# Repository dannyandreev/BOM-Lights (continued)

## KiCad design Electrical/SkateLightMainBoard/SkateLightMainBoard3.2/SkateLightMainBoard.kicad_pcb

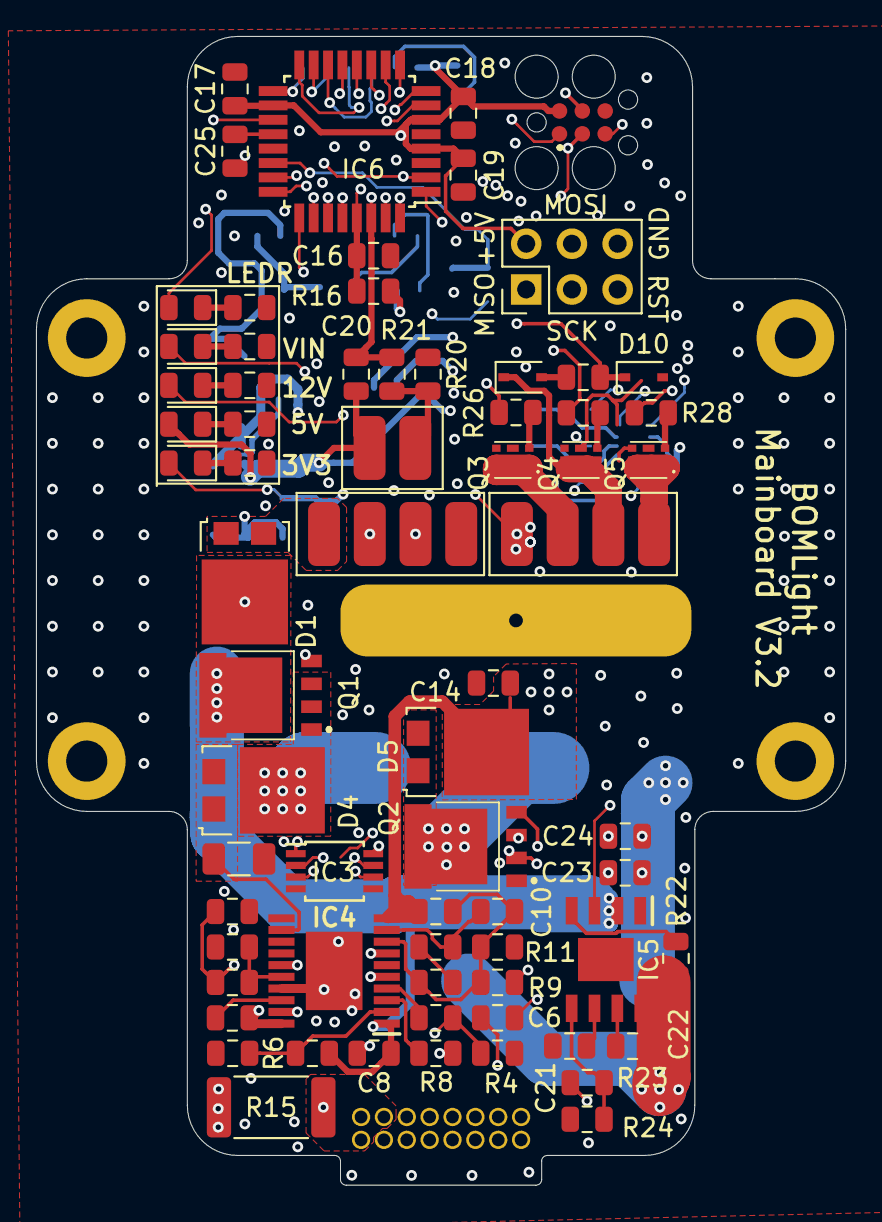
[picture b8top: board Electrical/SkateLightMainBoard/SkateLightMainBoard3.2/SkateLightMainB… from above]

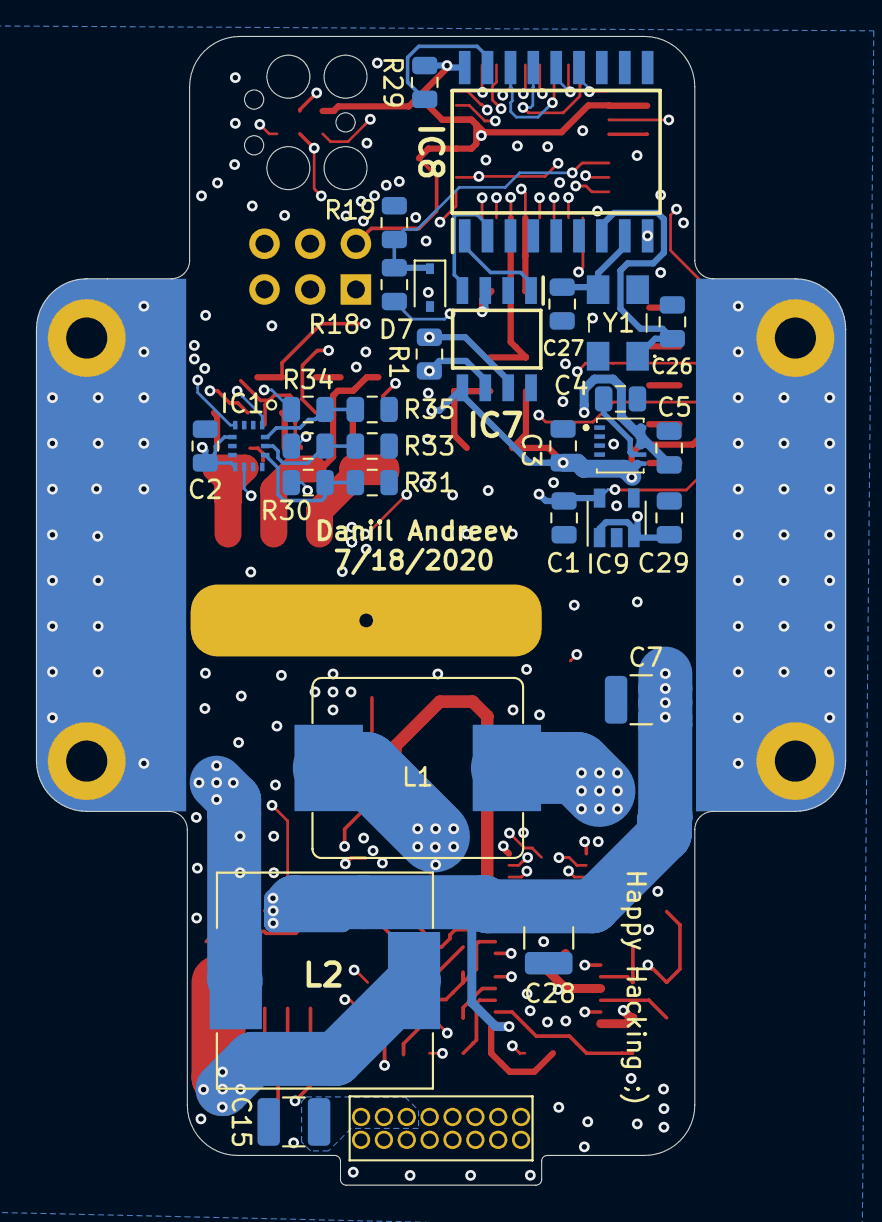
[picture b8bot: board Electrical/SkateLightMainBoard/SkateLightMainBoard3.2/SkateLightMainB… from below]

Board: 4 copper layers, 45.0 x 63.8 mm, 103 parts (31 on the bottom side), 78 nets.

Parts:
C1, C3, C23, C24: 10uF 16V; C_0805_2012Metric
C2, C16, C17, C18, C19, C20, C25: 0.1uF 25V; C_0805_2012Metric
C4, C13, C21, C29: 1uF 25V; C_0805_2012Metric
C5: 1uF 100V; C_0805_2012Metric
C6: 22nF 100V; C_0805_2012Metric
C7, C15, C28: 10uF 100V; C_1210_3225Metric
C8, C9, C11, C14, C22: 0.1uF 100V; C_0805_2012Metric
C10, C12: 2.2nF 100V; C_0805_2012Metric
C26, C27: 27pF 25V; C_0805_2012Metric
D1, D4, D5: D_Schottky_AAK; TO-277A
D2, D3, D8, D9: LEDO; LED_0805_2012Metric
D6: LEDR; LED_0805_2012Metric
D7, D10: 3V6 5%; D_SOD-323
D11: D; D_SOD-323
H1: MountingHole_Pad; ThermalPadV2_SkateLight_L
H2: MountingHole_Pad; ThermalPadV2_SkateLight_R
H3: MountingHole; Wire Slot 1
IC1: LSM6DS3USTR; LGA-14(2.5X3X0.86)
IC2: MAXM15062AMB+; MAXM15462AMB
IC3: MCP4132-502E_SN; TSSOP-8_3x3mm_P0.65mm
IC4: LM5118MH_NOPB; SOP65P640X110-21N
IC5: LMR36520FADDAR; SOIC127P600X170-9N
IC6: ATMEGA328P-AUR; TQFP-32_7x7mm_P0.8mm
IC7: MCP2562-E_SN; SOIC127P600X175-8N
IC8: MCP2515T-I_SO; SOIC127P1030X265-18N
IC9: AP2139AK-3.3TRG1; SOT-23-5
J1, J7: Conn_01x04_Male; 4 Wire Pad
J2: Conn_02x03_Odd_Even; PinHeader_2x03_P2.54mm_Vertical
J3: Conn_02x08_Odd_Even; Conn_2x8_0.05in
J4: TC2030-MCP; TC2030MCP
J6: Conn_01x02_Male; 2WirePad
L1: 97uH 2.7A; ‎ETQ-P5M101YGC‎ Inductor
L2: 7447709330‎ 33uH 4.2A 45MOHM; WE-PD_1260%2f1245%2f1280%2f121054
Q1, Q2: PSMN039-100YS,115; PSMN5R660YLX
Q3, Q4, Q5: FDMA410NZ
R1: 120 5%; R_0805_2012Metric
R2: 33k 5%; R_0805_2012Metric
R3, R31, R33, R35: 3k3 5%; R_0805_2012Metric
R4: 47k 5%; R_0805_2012Metric
R5: 1k 5%; R_0805_2012Metric
R6: 68k 5%; R_0805_2012Metric
R7, R12, R16, R21, R25, R29: 10k 5%; R_0805_2012Metric
R8: 20k5 1%; R_0805_2012Metric
R9: 330 1%; R_0805_2012Metric
R10: 47k 1%; R_0805_2012Metric
R11: 22k 1%; R_0805_2012Metric
R13: 36k5 1%; R_0805_2012Metric
R14: 0.03 1% 0.5W; R_1206_3216Metric
R15: 0.3 1% 1W; R_2512_6332Metric
R17: 1k5 5%; R_0805_2012Metric
R18, R20: 100k 5%; R_0805_2012Metric
R19: 4k7 5%; R_0805_2012Metric
R22: 100k %5; R_0805_2012Metric
R23: 100k 1%; R_0805_2012Metric
R24: 9.09 1%; R_0805_2012Metric
R26, R27, R28, R37: 330 5%; R_0805_2012Metric
R30, R32, R34: 2k2 5%; R_0805_2012Metric
R36: 1k2 5%; R_0805_2012Metric
Y1: ECS-80-18-30B-AGN-TR; ECS801830BAGNTR

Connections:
12V_CTRL: IC5.3, IC6.8
+3V3: C1.1, C2.1, D9.2, IC1.5, IC1.8, IC9.5
+5V: C3.1, C17.1, C18.1, C19.1, C20.1, C29.1, D3.2, IC2.5, IC2.6, IC3.8, IC6.4, IC6.6, IC6.18, IC7.3, IC7.5, IC8.18, IC9.1, IC9.3, J2.2, J3.13, J4.2, J6.2, R16.1, R29.1
+12V: C23.1, C24.1, D8.2, J7.4, L2.2, R23.2
/CAN Controller/CANH: IC7.7, J1.3, R1.2
/CAN Controller/CANL: IC7.6, J1.2, R1.1
Button: C20.2, IC6.30, R21.1
CTRLLEDB: IC6.13, R28.1
CTRLLEDG: IC6.10, R27.1
CTRLLEDR: IC6.9, R26.1
GND: C1.2, C2.2, C3.2, C4.2, C5.2, C6.2, C7.2, C8.2, C12.2, C13.2, C14.2, C15.2, C16.2, C17.2, C18.2, C19.2, C21.2, C23.2, C24.2, C25.2, C26.2, C27.2, C28.2, C29.2, D7.2, D10.2, H1.1, H2.1, IC1.2, IC1.3, IC1.6, IC1.7, IC2.2, IC3.4, IC3.5, IC4.6, IC4.13, IC4.14, IC4.17, IC4.21, IC5.1, IC5.9, IC6.3, IC6.5, IC6.21, IC7.2, IC7.8, IC8.9, IC9.2, J1.1, J2.6, J3.7, J4.6, Q2.1, Q2.2, Q2.3, Q3.4, Q3.8, Q4.4, Q4.8, Q5.4, Q5.8, R2.2, R3.2, R4.2, R7.2, R8.2, R11.2, R14.2, R15.2, R17.2, R19.2, R20.1, R24.1, R25.2, R31.2, R33.2, R35.2, R36.2, Y1.2, Y1.4
IMU_INT1: IC1.4, IC6.31
IMU_INT2: IC1.9, IC6.32
LED+: C14.1, C15.1, D5.3, IC4.10, J3.2, J3.4, J3.6, R10.1
LED-: IC6.19, J3.14, J3.15, J3.16, R15.1
LEDCTRL: IC6.1, R4.1, R5.2
LEDR: D6.2, IC6.2
LEDSign1: IC6.27, J3.11
LEDSign2: IC6.28, J3.12
LightSense1: IC6.25, J3.8
LightSense2: IC6.26, J3.9
NRST: C16.1, IC6.29, J2.5, J4.5, R16.2
unnamed: C4.1, IC2.7
unnamed: C6.1, IC4.7
unnamed: C9.1, R12.2
unnamed: C10.1, IC4.9, R12.1
unnamed: C9.2, C10.2, IC4.8, R9.1, R10.2, R11.1
unnamed: C11.1, D4.3, IC4.20, L1.1, Q1.1, Q1.2, Q1.3
unnamed: C11.2, IC4.18
unnamed: C12.1, IC4.5, R13.2
unnamed: C13.1, IC4.16, R13.1
unnamed: C21.1, IC5.6
unnamed: C22.1, IC5.8, L2.1, R22.2
unnamed: C22.2, IC5.7
unnamed: C25.1, IC6.20
unnamed: D1.1, D1.2, J1.4
unnamed: D2.1, R2.1
unnamed: D3.1, R3.1
unnamed: D4.1, D4.2, IC4.12, R14.1
unnamed: D5.1, D5.2, L1.2, Q2.5
unnamed: D6.1, R17.1
unnamed: D8.1, R25.1
unnamed: D9.1, R36.1
unnamed: D11.1, J7.2, Q4.1, Q4.2, Q4.5, Q4.6, Q4.7
unnamed: D11.2, R37.1
unnamed: IC1.12, R30.2, R31.1
unnamed: IC1.13, R32.2, R33.1
unnamed: IC1.14, R34.2, R35.1
unnamed: IC3.6, R9.2
unnamed: IC4.2, R6.2, R7.1
unnamed: IC4.3, R8.1
unnamed: IC4.4, R5.1
unnamed: IC4.15, Q2.4
unnamed: IC4.19, Q1.4
unnamed: IC5.4, R22.1
unnamed: IC5.5, R23.1, R24.2
unnamed: IC7.1, IC8.1
unnamed: IC7.4, IC8.2
unnamed: IC8.17, R29.2
unnamed: J6.1, R20.2, R21.2
unnamed: J7.1, Q5.1, Q5.2, Q5.5, Q5.6, Q5.7
unnamed: J7.3, Q3.1, Q3.2, Q3.5, Q3.6, Q3.7
unnamed: Q3.3, R26.2
unnamed: Q4.3, R27.2
unnamed: Q5.3, R28.2
OSC1: C27.1, IC8.8, Y1.3
OSC2: C26.1, IC8.7, Y1.1
SPI_CAN_CS: IC6.14, IC8.16
SPI_DPOT_CS: IC3.1, IC6.11
SPI_IMU_CS: IC6.12, R30.1
SPI_MISO: IC1.1, IC3.7, IC6.16, IC8.15, J2.1, J4.1
SPI_MOSI: IC3.3, IC6.15, IC8.14, J2.4, J4.4, R34.1
SPI_SCK: IC3.2, IC6.17, IC8.13, J2.3, J4.3, R32.1
Temp1: IC6.23, J3.10
Temp2: IC6.24, J3.1
VCC: C5.1, C7.1, C8.1, C28.1, D1.3, D2.2, IC2.8, IC2.9, IC2.10, IC4.1, IC5.2, Q1.5, R6.1, R18.1
VINADC: D7.1, IC6.22, R18.2, R19.1
WS2811DI: D10.1, IC6.7, R37.2

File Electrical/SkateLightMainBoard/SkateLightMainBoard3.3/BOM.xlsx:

| Designator | Package | Designation | Supplier and ref | Quantity | Note
1 | Q2,Q1 | PSMN5R660YLX | PSMN039-100YS,115 | PSMN039-100YS | 2
2 | IC8 | SOIC127P600X175-8N | MCP2562-E_SN | MCP2562T-E/SN | 1
3 | L2 | WE-PD_1260%2f1245%2f1280%2f121054 | 7447709330â€Ž 33uH 4.2A 45MOHM | 7447709330 | 1
4 | L1 | â€ŽETQ-P5M101YGCâ€Ž Inductor | 97uH 2.7A | ETQ-P5M101YGC | 1
5 | C17,C2,C16,C18,C19,C20,C25 | C_0805_2012Metric | 0.1uF 25V | C0805C104Z3VACT | 7
6 | IC1 | LGA-14(2.5X3X0.86) | LSM6DS3USTR | LSM6DS3USTR | 1
7 | R7,R12,R16,R21,R25,R29 | R_0805_2012Metric | 10k 5% | RMCF0805JT10K0 | 6
8 | R6 | R_0805_2012Metric | 68k 5% | RMCF0805JT68K0 | 1
9 | R9 | R_0805_2012Metric | 330 1% | RMCF0805FT330R | 1
10 | J3 | Conn_2x8_0.05in | NOT POPULATED |  | 0
11 | C6 | C_0805_2012Metric | 22nF 100V | CC0805KRX7R0BB223 | 1
12 | C7,C15,C28 | C_1210_3225Metric | 10uF 100V | GRM32EC72A106KE05L | 3
13 | C8,C9,C11,C14,C22 | C_0805_2012Metric | 0.1uF 100V | CC0805KKX7R0BB104 | 5
14 | C10,C12 | C_0805_2012Metric | 2.2nF 100V | C0805C222K1RACTU | 2
15 | C13,C4,C21,C29 | C_0805_2012Metric | 0.1uF 25V | C0805C104Z3VACT | 4
16 | D2,D3,D8,D9 | LED_0805_2012Metric | NOT POPULATED | LEDO | 0
17 | D4,D5,D1 | TO-277A | D_Schottky_AAK | FSV8100V | 3
18 | IC3 | TSSOP-8_3x3mm_P0.65mm | MCP4132-502E_SN | MCP4132T-502E/MS | 1
19 | IC4 | SOP65P640X110-21N | LM5118MH_NOPB | LM5118Q1MHX/NOPB | 1
20 | R1 | R_0805_2012Metric | 120 5% | RMCF0805JT120R | 1
21 | R2 | R_0805_2012Metric | 33k 5% | RMCF0805JT33K0 | 1
22 | R3,R31,R33,R35 | R_0805_2012Metric | 3k3 5% | RMCF0805JT1K20 | 4
23 | R4 | R_0805_2012Metric | 47k 5% | RMCF0805JT47K0 | 1
24 | R5,R38 | R_0805_2012Metric | 1k 5% | RMCF0805JT1K00 | 2
25 | R8 | R_0805_2012Metric | 20k5 1% | RMCF0805FT20K5 | 1
26 | R10 | R_0805_2012Metric | 47k 1% | RMCF0805FT47K0 | 1
27 | R11 | R_0805_2012Metric | 22k 1% | RMCF0805FT22K0 | 1
28 | R13 | R_0805_2012Metric | 36k5 1% | RMCF0805FT36K5 | 1
29 | R15 | R_2512_6332Metric | 0.3 1% 1W | RL2512FK-070R3L | 1
30 | C5 | C_0805_2012Metric | 0.1uF 100V | CC0805KKX7R0BB104 | 1
31 | C3,C1 | C_0805_2012Metric | 10uF 10V | C0805C106K8PACTU | 2
32 | D6 | LED_0805_2012Metric | NOT POPULATED | LEDR | 0
33 | IC2 | MAXM15462AMB | MAXM15063AMB+ | MAXM15063AMB+ | 1 | Pin one is designated by the cross, not the white dot on the IC.
34 | J4 | TC2030MCP | NOT POPULATED | TC2030-MCP | 0
35 | J6,J5 | 2WirePad | NOT POPULATED | Conn_01x02_Male | 0
36 | R17 | R_0805_2012Metric | 1k5 5% | RMCF0805JT1K50 | 1
37 | R20,R18 | R_0805_2012Metric | 100k 5% | RMCF0805JT100K | 2
38 | J1,J7 | 4 Wire Pad | NOT POPULATED | Conn_01x04_Male | 2
39 | R14 | R_1206_3216Metric | 0.03 1% 0.5W | CSR1206FK30L0 | 1
40 | H1 | ThermalPadV2_SkateLight_L | NOT POPULATED | MountingHole_Pad | 0
41 | H2 | ThermalPadV2_SkateLight_R | NOT POPULATED | MountingHole_Pad | 0
42 | R19 | R_0805_2012Metric | 4k7 5% | RMCF0805JT4K70 | 1
43 | D7,D10 | D_SOD-323 | 3v6 5% | MM3Z3V6T1G | 2
44 | C23,C24 | C_0805_2012Metric | 10uF 16V | C0805C106K4PACTU | 2
45 | C26,C27 | C_0805_2012Metric | 27pF 50V | C0805C270J5GACTU | 2
46 | D11 | D_SOD-323 | D | BAT54HT1G | 1
47 | IC6 | TQFP-32_7x7mm_P0.8mm | ATMEGA328P-AUR | ATMEGA328P-AUR | 1
48 | IC7 | SOIC127P600X175-8N | MCP2562-E_SN | MCP2562T-E/SN | 1
49 | IC9 | SOT-23-5 | AP2139AK-3.3TRG1 | AP2139AK-3.3TRG1 | 1
50 | Q3,Q4,Q5,Q6 | FDMA410NZ | FDMA410NZ | FDMA410NZ | 4
51 | R22 | R_0805_2012Metric | 100k 5% | RMCF0805JT100K | 1
52 | R23 | R_0805_2012Metric | 100k 1% | RC0805FR-07100KL | 1
53 | R24 | R_0805_2012Metric | 9.09k 1% | RMCF0805FT9K09CT-ND | 1
54 | R26,R27,R28,R37,R40 | R_0805_2012Metric | 330 5% | RMCF0805JT330RCT-ND | 5
55 | R30,R32,R34 | R_0805_2012Metric | 2k2 5% | RMCF0805JT2K20CT-ND | 3
56 | R36 | R_0805_2012Metric | 1k2 5% | RMCF0805JT1K20CT-ND | 1
57 | Y1 | ECS801830BAGNTR | ECS-80-18-30B-AGN-TR | XC2709CT-ND | 1
58 | IC5 | SOIC127P600X170-9N | LMR36520FADDAR | 296-LMR36520FADDARCT-ND | 1
59 | J2 | PinHeader_2x03_P2.54mm_Vertical | NOT POPULATED | Conn_02x03_Odd_Even | 0
60 | R39 | R_0805_2012Metric | 47k 5% | RMCF0805JT47K0 | 1

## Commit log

2022-03-13 open sourcing under GNU 3.0
